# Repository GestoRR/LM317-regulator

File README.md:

Simple design of a regulated power supply based on the LM317 stabilized regulator

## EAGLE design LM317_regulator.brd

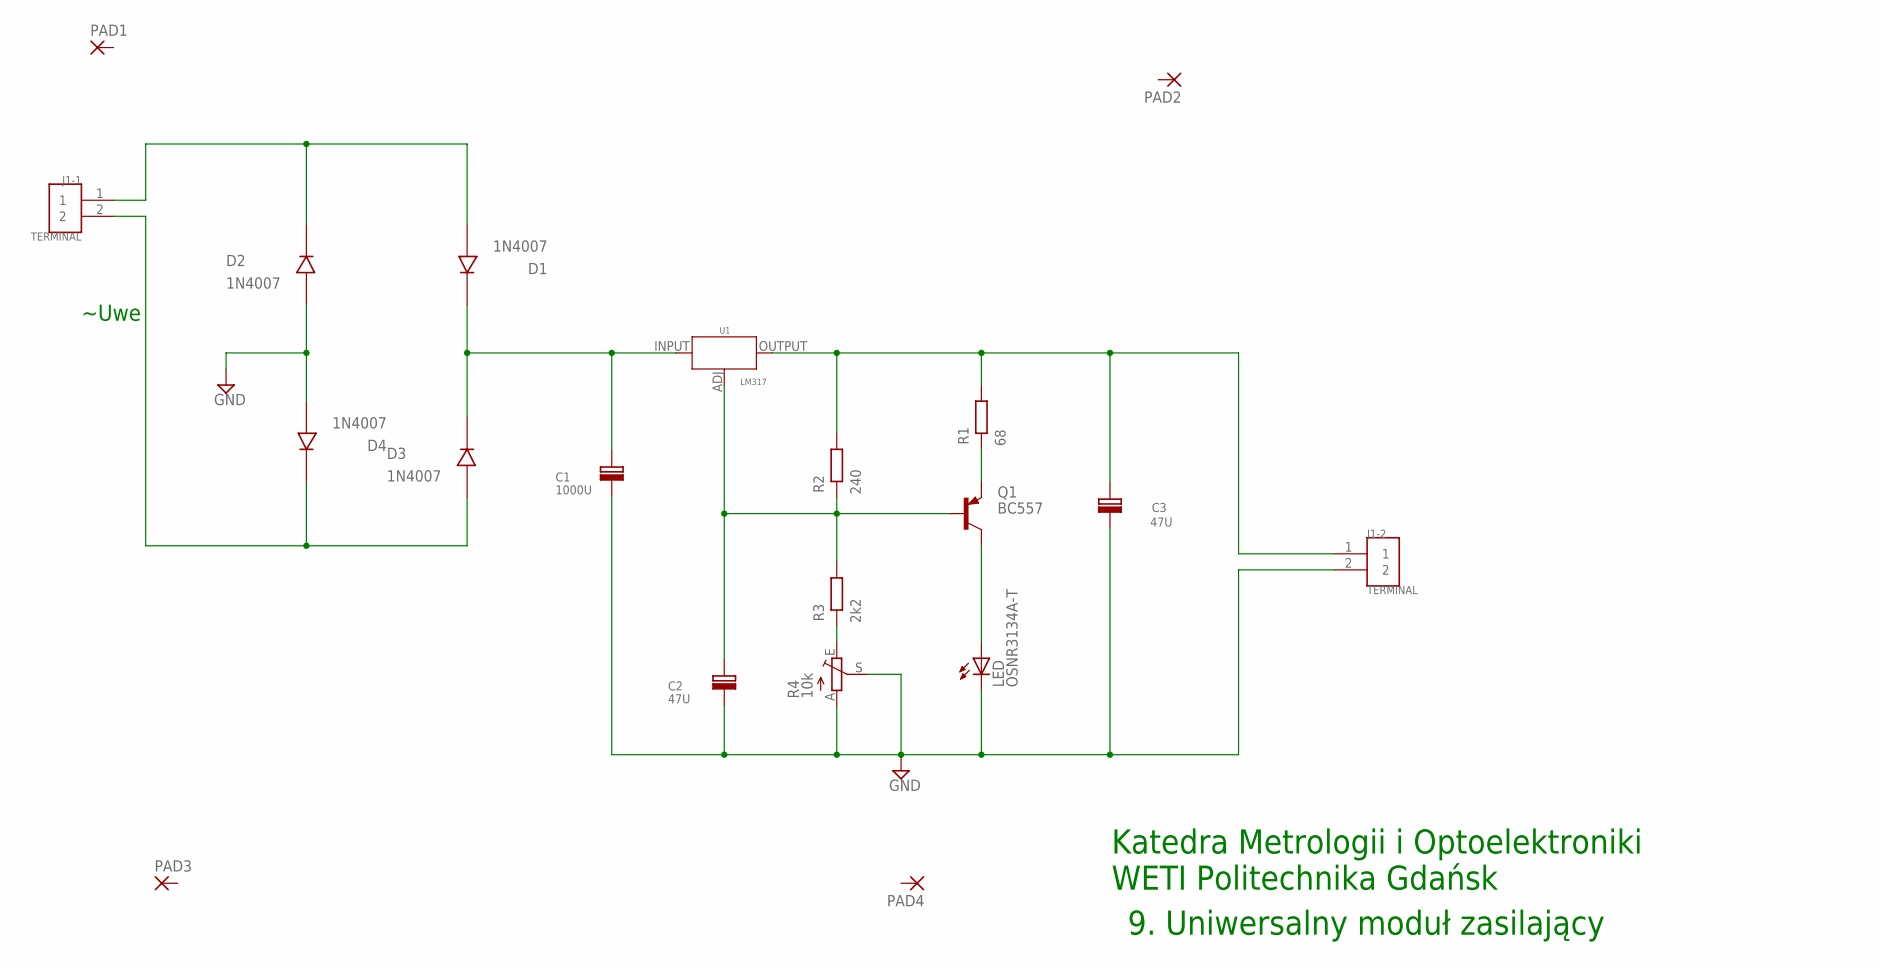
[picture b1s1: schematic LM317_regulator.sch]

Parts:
C1: 1000U
C2, C3: 47U
D1, D2, D3, D4: 1N4007
J1-1, J1-2: TERMINAL
LED: OSNR3134A-T; LED3MM
PAD1, PAD2, PAD3, PAD4: 2,54/1,1
Q1: BC557; TO92-EBC
R1: 68; 1206
R2: 240; 1206
R3: 2k2; 1206
R4: 10k; CA6V
U1: LM317

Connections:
GND: C1.L, C2.L, C3.L, D2.A (L), D4.A (L), J1-2.2, LED.K (C), R4.A, R4.S
unnamed: R3.1 (H), R4.E
unnamed: C1.H, D1.C (H), D3.C (H), U1.INPUT (IN)
unnamed: D3.A (L), D4.C (H), J1-1.2
unnamed: D1.A (L), D2.C (H), J1-1.1
unnamed: C2.H, Q1.B, R2.1 (H), R3.2 (L), U1.ADJ
unnamed: Q1.E, R1.1 (H)
unnamed: C3.H, J1-2.1, R1.2 (L), R2.2 (L), U1.OUTPUT (OUT)
unnamed: LED.A, Q1.C

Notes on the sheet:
9. Uniwersalny moduł zasilający
Katedra Metrologii i Optoelektroniki WETI Politechnika Gdańsk
~Uwe

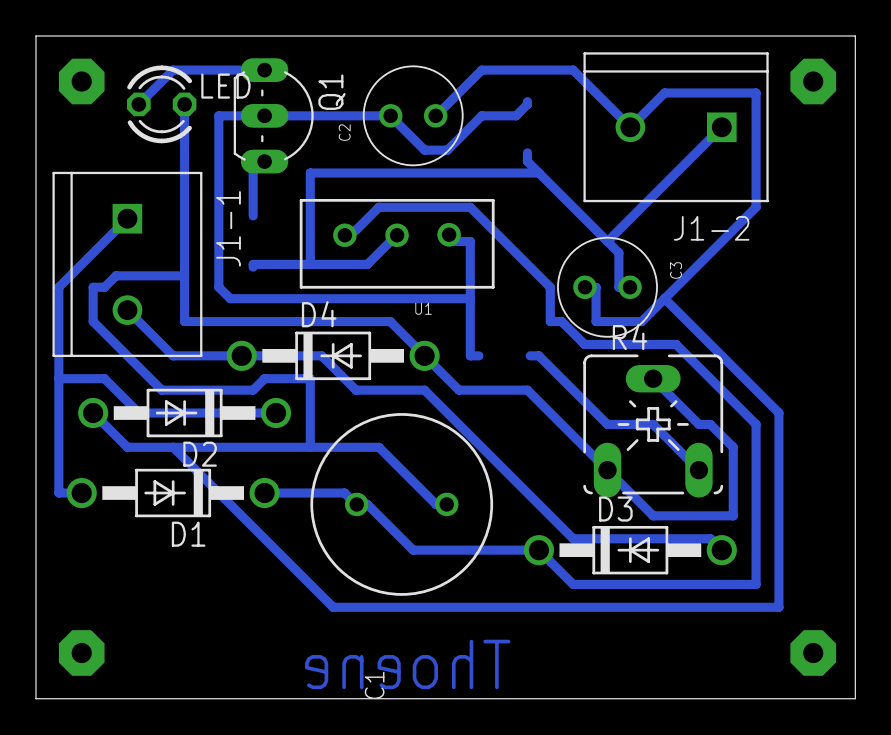
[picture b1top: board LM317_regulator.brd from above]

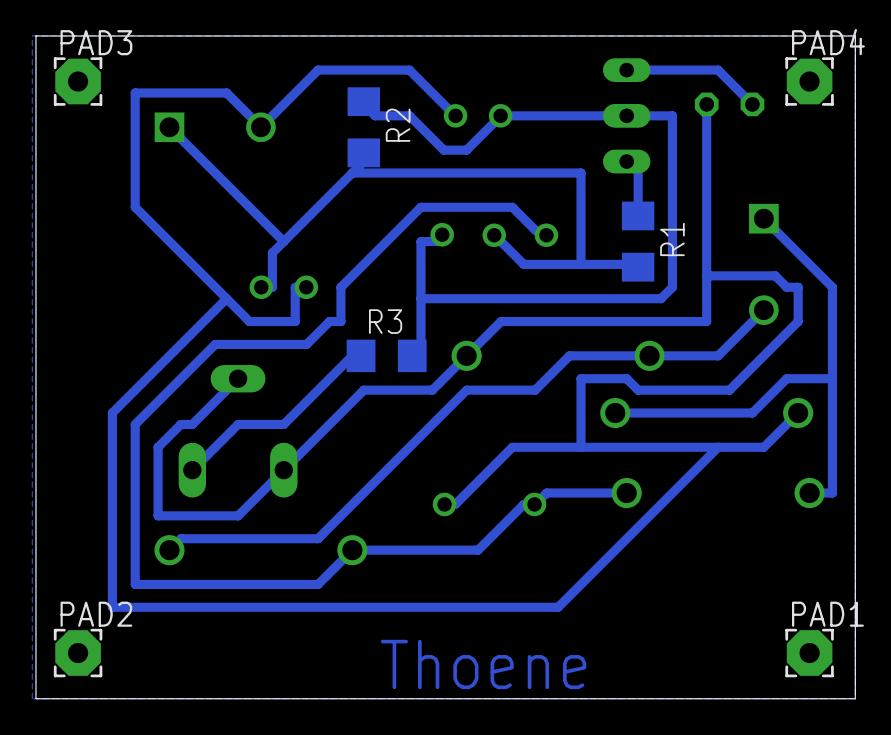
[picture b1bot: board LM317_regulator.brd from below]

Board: 2 copper layers, 45.5 x 36.8 mm, 20 parts (7 on the bottom side), 9 nets.

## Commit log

2024-07-14 LM317 power supply
